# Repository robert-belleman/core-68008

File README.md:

# core-68008
Single-board 68008 system with a Elektor Junior bus interface

The core68008 board is a complete MC68008 computer on one 160 x 100 mm,
4-layer PCB: CPU, 512K RAM, 256K flash, a 68681 DUART for the serial console
and a bridge that runs cards for the Elektor Junior bus at 1 MHz. It boots
into the MON68K monitor, which includes Enhanced BASIC.

Status (2026-11-24): the first PCBs are built and run the monitor from
flash over the FTDI serial link. See [Known issues](#known-issues-and-changes-for-the-next-revision)
for the fixes made on the bench.

## Specifications

| | |
|---|---|
| CPU | MC68008P8 (48-pin DIP, 20 address lines), 8 MHz from oscillator X1 |
| RAM | 512K static RAM, AS6C4008-55 (U4) |
| ROM | 256K flash, SST39SF020A-70 PLCC-32 (U5), programmable in circuit |
| Serial | MC68681 DUART (U6), 3.6864 MHz crystal Y1. Channel A is the console on J2 (FTDI TTL-232R-5V pinout), 38400 8N1, RTS/CTS |
| Expansion | Elektor Junior bus on J1 (DIN 41612, a+c), 64K window at $C0000, 1 MHz PHI2 |
| Glue logic | three ATF22V10C GALs (see below) and a 74LS07 |
| Reset | DS1233-5 power-on reset (U14) and reset button SW1 |
| Interrupts | level 5 = 68681 (vectored), level 2 = Junior IRQ, level 7 = Junior NMI (autovectored) |
| Other | logic analyser header J4, DUART I/O header J3, prototyping area PROTO1 (7 x 20 holes) |

## Memory map

| Range | Device |
|---|---|
| $00000-$7FFFF | SRAM (at reset the boot overlay maps the flash here for reads) |
| $80000-$BFFFF | Flash: MON68K at $80000, EhBASIC at $A0000 |
| $C0000-$CFFFF | Junior bus window (1 MHz bus cycles) |
| $D0000-$EFFFF | unused, bus error |
| $F0000-$FFFFF | 68681 DUART (16 registers, repeated) |

The boot overlay is set by the power-on reset and switched off by the first
access to $80000-$BFFFF, so the CPU fetches its reset vectors from flash.
The monitor's own view of this map, with its workspace and the default
user registers, is in [monitor/MONITOR.md](monitor/MONITOR.md#memory-map-as-the-monitor-sees-it).

## Hardware

The schematic is a hierarchical KiCad 10 project, `core68008.kicad_pro`:

| Sheet | Contents |
|---|---|
| `cpu.kicad_sch` | MC68008 (U1), 74LS07 open-collector drivers (U12), pull-ups, LEDs HALT, RESET and BERR, logic analyser header J4 |
| `memory.kicad_sch` | GAL1 decode (U2), SRAM (U4), flash (U5) |
| `duart.kicad_sch` | 68681 (U6) with crystal Y1, FTDI header J2 (JP3 connects the cable's 5V), I/O header J3, LEDs D5 (OP6) and D6 (OP7) |
| `bridge.kicad_sch` | GAL2 bridge (U3), GAL3 busdbg (U11), 74LS245 buffers (U7-U9), 74HCT573 read latch (U10), Junior bus connector J1 |
| `power.kicad_sch` | 8 MHz oscillator X1, DS1233 reset (U14), reset button, decoupling |

The PCB is `core68008.kicad_pcb`; extra footprints are in `core68008.pretty/`.

### GALs

The GAL sources are in [gal/](gal/) and are built with galasm 2.1
(`make`, `make prog-decode` etc., see the header of [gal/Makefile](gal/Makefile)).
Each `.pld` file explains its equations.

| GAL | Source | Function |
|---|---|---|
| GAL1 (U2) | [decode.pld](gal/decode.pld) | address decoding, boot overlay, DTACK, BERR, RAM/ROM/DUART selects, /RD and /WR |
| GAL2 (U3) | [bridge.pld](gal/bridge.pld) | Junior bus bridge: PHI2 = CLK/8 (1 MHz, locked to the CPU clock), buffer enables, read latch, DTACK after PHI2 falls; interrupt acknowledge (VPA) |
| GAL3 (U11) | [busdbg.pld](gal/busdbg.pld) | bus clocks PHI1/PHI2, bus R/W, RAM.RW, sticky BERR LED, logic analyser trigger and debug outputs DBG0-DBG3 |
| GAL1 (temporary) | [decode_boot.pld](gal/decode_boot.pld) | only for FLASHBOOT, with a 27128 EPROM in the SRAM socket |

### LEDs

| LED | Meaning |
|---|---|
| D2 | power |
| D3, D4 | HALT, RESET |
| D7 | bus error has happened since reset (latched by GAL3) |
| D6 | 68681 OP7: monitor active |
| D5 | 68681 OP6: user LED |

## Software

| Directory | What it is | Documentation |
|---|---|---|
| [monitor/](monitor/) | MON68K, the ROM monitor: memory and register commands, S-record loading (`LO`), disassembler, breakpoints, tracing, a TRAP #15 API for user programs, and `FL` to reprogram the flash from RAM | [MONITOR.md](monitor/MONITOR.md) |
| [monitor/basic/](monitor/basic/) | Lee Davison's Enhanced BASIC 3.54 at $A0000. Start it with `BA` (cold) or `BW` (warm); `BYE` returns to the monitor | [MONITOR.md, EhBASIC](monitor/MONITOR.md#ehbasic-ba-bw) |
| [monitor/flashupd/](monitor/flashupd/) | FLASHUPD: loads a new monitor into the flash from a monitor that doesn't have `FL` yet | [MONITOR.md, FLASHUPD](monitor/MONITOR.md#the-first-time-flashupd) |
| [monitor/examples/](monitor/examples/) | example user programs and the API include file `mon68k.inc` | [MONITOR.md, API](monitor/MONITOR.md#api-for-user-programs-trap-15) |
| [monitor/test/](monitor/test/) | board emulator (Musashi core, with 68681 and SST39SF020A models) and test scripts | [test/README.md](monitor/test/README.md) |
| [flashboot/](flashboot/) | SERTEST and FLASHBOOT: program the flash in circuit from a 27128 EPROM in the SRAM socket, plus `term.py`, a terminal for odd baud rates on macOS | [flashboot/README.md](flashboot/README.md) |
| [Basic/](Basic/) | BASIC programs (a Mandelbrot plot) | |
| [breadboard/](breadboard/) | test programs and logs from the earlier breadboard version | [review.md](breadboard/review.md) |

### Tools

* [vasm](http://sun.hasenbraten.de/vasm/) (`vasmm68k_mot`, Motorola syntax) for all 68000 code. The Makefiles expect `/opt/homebrew/bin/vasmm68k_mot`; override with `make VASM=...`.
* galasm 2.1 for the GALs (`make GALASM=...` to override).
* A T48 programmer with `minipro` for the GALs, the EPROM and the flash (the flash needs a PLCC32 adapter).
* Python 3 for the host scripts (`flashboot.py`, `term.py`, `bin2srec.py`).

### Quick start

```
cd monitor && make          # monitor.bin, the 256K flash image
make flash                  # program it with the T48, or:
make s28                    # monitor.s28, to load with LO and program with FL
```

Connect the FTDI cable to J2 and open a terminal at 38400 8N1 with RTS/CTS.
After reset the monitor shows its banner and the `>` prompt; `HE` lists the
commands. To put a monitor with `FL` on a board whose monitor doesn't have
`FL` yet, use FLASHUPD (`make flashupd`); on a blank board use the T48 or
FLASHBOOT.

## Known issues and changes for the next revision

Found during bring-up of the first PCBs:

* **RxDA pull-up too strong.** The USB-serial module's TX could only pull
  RxDA (via the 10k in RN2) down to about 2.4 V, so the 68681 received
  nothing. Workaround: RN2 removed. Next revision: a separate 100k pull-up on RxDA.
* **~BR floats** now that RN2 is out, because RN2 also pulls up ~BR. Refit RN2
  with its RxDA pin clipped, or fit a 10k pull-up on ~BR.
* **68681 crystal doesn't start reliably** (it runs at about 100 kHz unless the
  board is touched). The 68681 data sheet asks for unequal load capacitors,
  but C2 and C3 are both 22 pF. Change C2 (X1, pin 32) to 12-15 pF and C3
  (X2, pin 33) to 0-5 pF. 12 pF and 4.7 pF are verified to work. An option for a
  3.6864 MHz oscillator can would also help.
* **~VPA and ~IACK5** are driven only by GAL2 and have no pull-ups, so they
  float when GAL2 is not fitted. Add pull-ups.
* **XDTACK** pull-up: use a separate 1k resistor instead of the RN1 element.

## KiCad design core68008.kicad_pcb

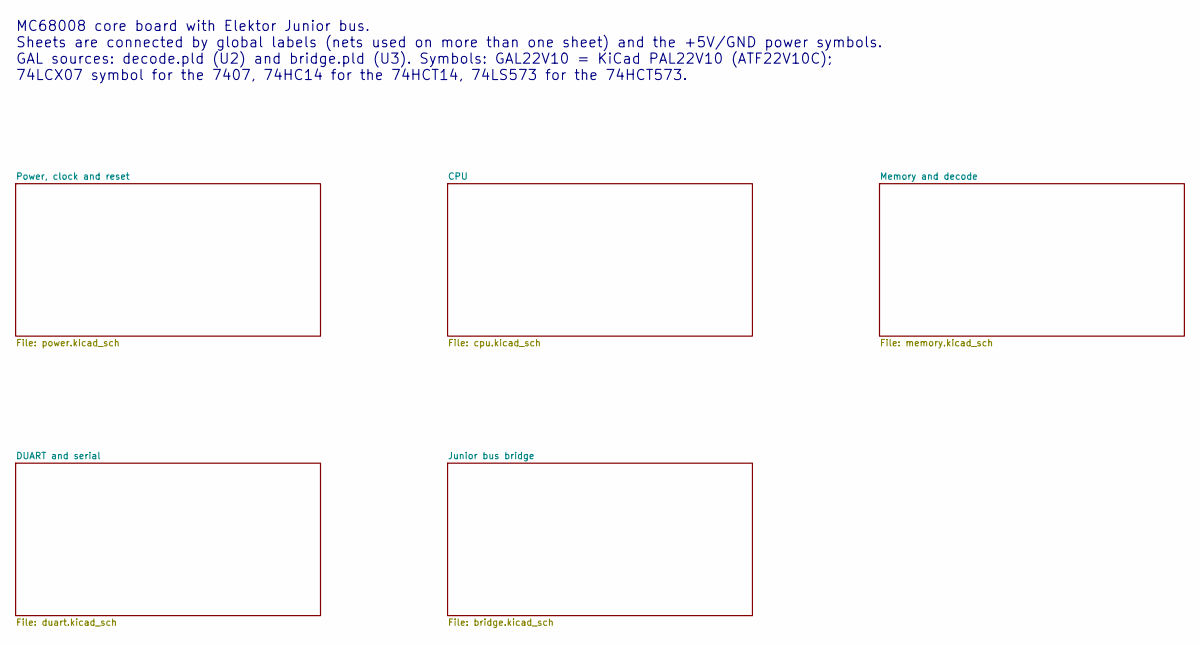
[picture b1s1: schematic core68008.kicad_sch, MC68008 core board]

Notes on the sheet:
MC68008 core board with Elektor Junior bus. Sheets are connected by global labels (nets used on more than one sheet) and the +5V/GND power symbols. GAL sources: decode.pld (U2) and bridge.pld (U3). Symbols: GAL22V10 = KiCad PAL22V10 (ATF22V10C); 74LCX07 symbol for the 7407, 74HC14 for the 74HCT14, 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

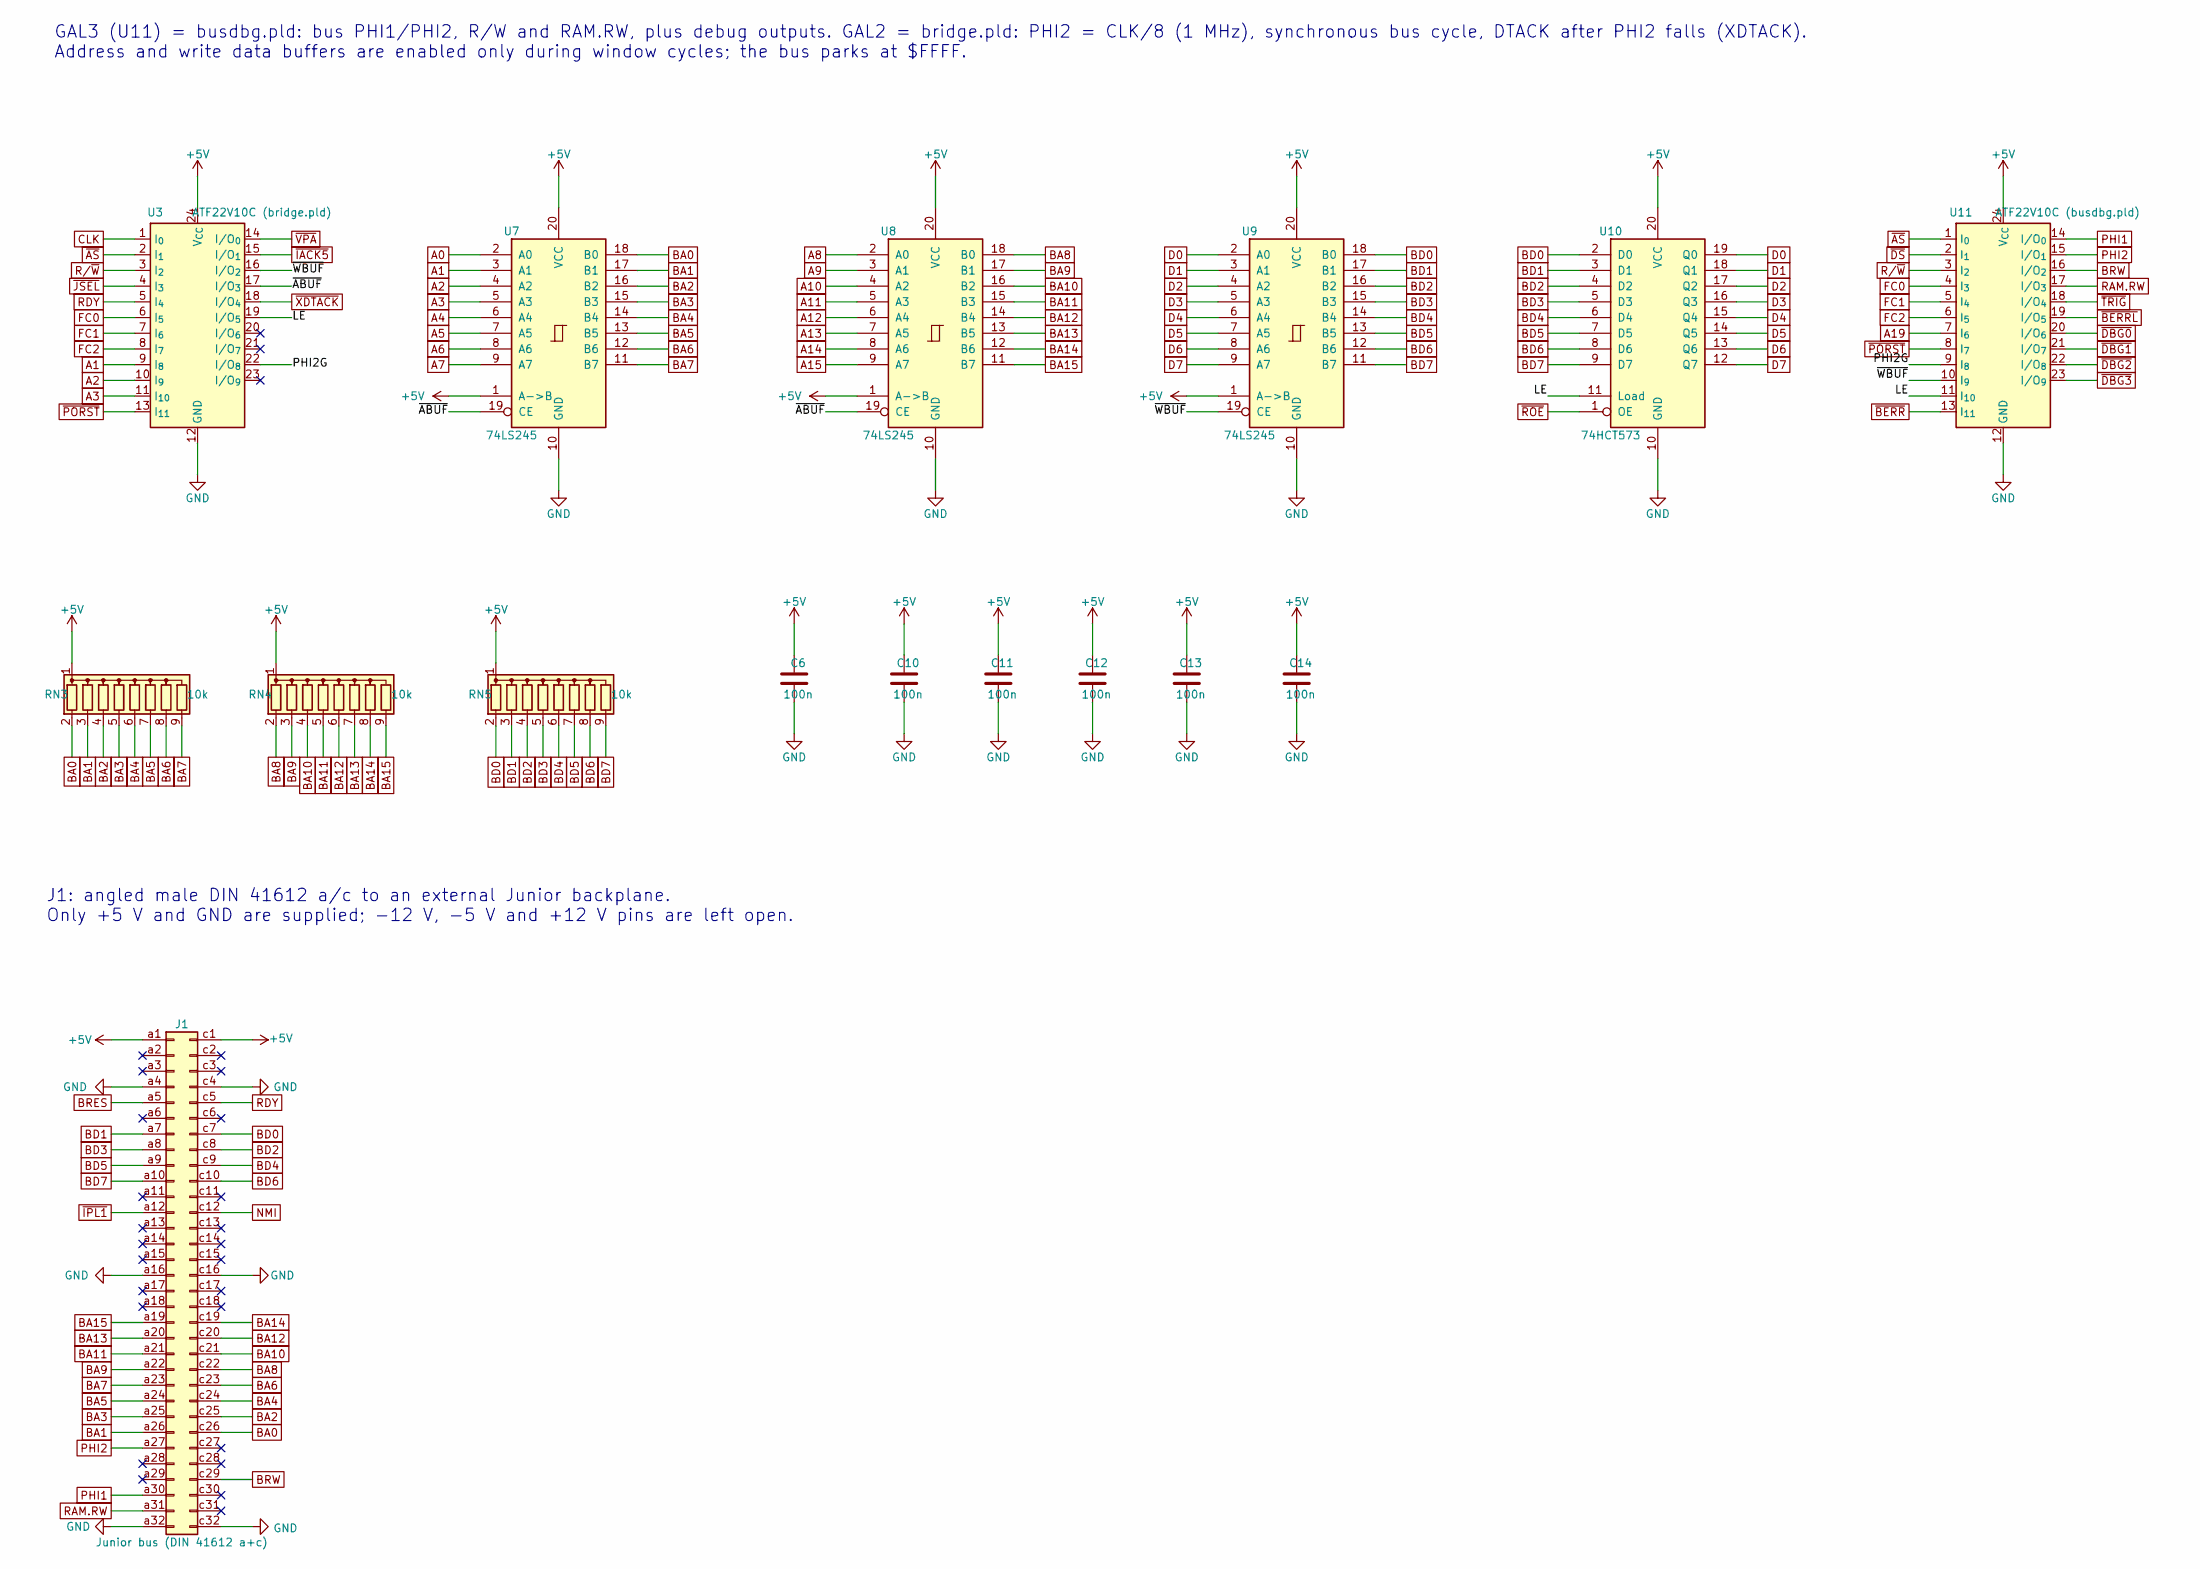
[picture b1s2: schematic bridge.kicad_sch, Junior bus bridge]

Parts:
C6, C10, C11, C12, C13, C14: 100n; C_Disc_D5.0mm_W2.5mm_P5.00mm
J1: Junior bus (DIN 41612 a+c); DIN41612_C_2x32_Male_Horizontal_THT_LongPads
RN3, RN4, RN5: 10k; R_Array_SIP9
U3: ATF22V10C (bridge.pld); DIP-24_W7.62mm_Socket_LongPads
U7, U8, U9: 74LS245; DIP-20_W7.62mm_Socket_LongPads
U10: 74HCT573; DIP-20_W7.62mm_Socket_LongPads
U11: ATF22V10C (busdbg.pld); DIP-24_W7.62mm_Socket_LongPads

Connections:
+5V: C6.1, C10.1, C11.1, C12.1, C13.1, C14.1, J1.a1, J1.c1, RN3.1 (common), RN4.1 (common), RN5.1 (common), U3.24 (V_{CC}), U7.1 (A->B), U7.20 (VCC), U8.1 (A->B), U8.20 (VCC), U9.1 (A->B), U9.20 (VCC), U10.20 (VCC), U11.24 (V_{CC}); also elsewhere on the board
/Junior bus bridge/LE: U3.19 (I/O_{5}), U10.11 (Load), U11.11 (I_{10})
/Junior bus bridge/PHI2G: U3.22 (I/O_{8}), U11.9 (I_{8})
/Junior bus bridge/~ABUF: U3.17 (I/O_{3}), U7.19 (CE), U8.19 (CE)
/Junior bus bridge/~WBUF: U3.16 (I/O_{2}), U9.19 (CE), U11.10 (I_{9})
A0: U7.2 (A0); also elsewhere on the board
A1: U3.9 (I_{8}), U7.3 (A1); also elsewhere on the board
A2: U3.10 (I_{9}), U7.4 (A2); also elsewhere on the board
A3: U3.11 (I_{10}), U7.5 (A3); also elsewhere on the board
A4: U7.6 (A4); also elsewhere on the board
A5: U7.7 (A5); also elsewhere on the board
A6: U7.8 (A6); also elsewhere on the board
A7: U7.9 (A7); also elsewhere on the board
A8: U8.2 (A0); also elsewhere on the board
A9: U8.3 (A1); also elsewhere on the board
A10: U8.4 (A2); also elsewhere on the board
A11: U8.5 (A3); also elsewhere on the board
A12: U8.6 (A4); also elsewhere on the board
A13: U8.7 (A5); also elsewhere on the board
A14: U8.8 (A6); also elsewhere on the board
A15: U8.9 (A7); also elsewhere on the board
A19: U11.7 (I_{6}); also elsewhere on the board
BA0: J1.c26, RN3.2 (R1), U7.18 (B0)
BA1: J1.a26, RN3.3 (R2), U7.17 (B1)
BA2: J1.c25, RN3.4 (R3), U7.16 (B2)
BA3: J1.a25, RN3.5 (R4), U7.15 (B3)
BA4: J1.c24, RN3.6 (R5), U7.14 (B4)
BA5: J1.a24, RN3.7 (R6), U7.13 (B5)
BA6: J1.c23, RN3.8 (R7), U7.12 (B6)
BA7: J1.a23, RN3.9 (R8), U7.11 (B7)
BA8: J1.c22, RN4.2 (R1), U8.18 (B0)
BA9: J1.a22, RN4.3 (R2), U8.17 (B1)
BA10: J1.c21, RN4.4 (R3), U8.16 (B2)
BA11: J1.a21, RN4.5 (R4), U8.15 (B3)
BA12: J1.c20, RN4.6 (R5), U8.14 (B4)
BA13: J1.a20, RN4.7 (R6), U8.13 (B5)
BA14: J1.c19, RN4.8 (R7), U8.12 (B6)
BA15: J1.a19, RN4.9 (R8), U8.11 (B7)
BD0: J1.c7, RN5.2 (R1), U9.18 (B0), U10.2 (D0)
BD1: J1.a7, RN5.3 (R2), U9.17 (B1), U10.3 (D1)
BD2: J1.c8, RN5.4 (R3), U9.16 (B2), U10.4 (D2)
BD3: J1.a8, RN5.5 (R4), U9.15 (B3), U10.5 (D3)
BD4: J1.c9, RN5.6 (R5), U9.14 (B4), U10.6 (D4)
BD5: J1.a9, RN5.7 (R6), U9.13 (B5), U10.7 (D5)
BD6: J1.c10, RN5.8 (R7), U9.12 (B6), U10.8 (D6)
BD7: J1.a10, RN5.9 (R8), U9.11 (B7), U10.9 (D7)
BRES: J1.a5; also elsewhere on the board
BRW: J1.c29, U11.16 (I/O_{2})
CLK: U3.1 (I_{0}); also elsewhere on the board
D0: U9.2 (A0), U10.19 (Q0); also elsewhere on the board
D1: U9.3 (A1), U10.18 (Q1); also elsewhere on the board
D2: U9.4 (A2), U10.17 (Q2); also elsewhere on the board
D3: U9.5 (A3), U10.16 (Q3); also elsewhere on the board
D4: U9.6 (A4), U10.15 (Q4); also elsewhere on the board
D5: U9.7 (A5), U10.14 (Q5); also elsewhere on the board
D6: U9.8 (A6), U10.13 (Q6); also elsewhere on the board
D7: U9.9 (A7), U10.12 (Q7); also elsewhere on the board
FC0: U3.6 (I_{5}), U11.4 (I_{3}); also elsewhere on the board
FC1: U3.7 (I_{6}), U11.5 (I_{4}); also elsewhere on the board
FC2: U3.8 (I_{7}), U11.6 (I_{5}); also elsewhere on the board
GND: C6.2, C10.2, C11.2, C12.2, C13.2, C14.2, J1.a4, J1.a16, J1.a32, J1.c4, J1.c16, J1.c32, U3.12 (GND), U7.10 (GND), U8.10 (GND), U9.10 (GND), U10.10 (GND), U11.12 (GND); also elsewhere on the board
NMI: J1.c12; also elsewhere on the board
PHI1: J1.a30, U11.14 (I/O_{0})
PHI2: J1.a27, U11.15 (I/O_{1}); also elsewhere on the board
RAM.RW: J1.a31, U11.17 (I/O_{3})
RDY: J1.c5, U3.5 (I_{4}); also elsewhere on the board
R/~W: U3.3 (I_{2}), U11.3 (I_{2}); also elsewhere on the board
~AS: U3.2 (I_{1}), U11.1 (I_{0}); also elsewhere on the board
~BERRL: U11.19 (I/O_{5}); also elsewhere on the board
~BERR: U11.13 (I_{11}); also elsewhere on the board
~DBG0: U11.20 (I/O_{6}); also elsewhere on the board
~DBG1: U11.21 (I/O_{7}); also elsewhere on the board
~DBG2: U11.22 (I/O_{8}); also elsewhere on the board
~DBG3: U11.23 (I/O_{9}); also elsewhere on the board
~DS: U11.2 (I_{1}); also elsewhere on the board
~IACK5: U3.15 (I/O_{1}); also elsewhere on the board
~IPL1: J1.a12; also elsewhere on the board
~JSEL: U3.4 (I_{3}); also elsewhere on the board
~PORST: U3.13 (I_{11}), U11.8 (I_{7}); also elsewhere on the board
~ROE: U10.1 (OE); also elsewhere on the board
~TRIG: U11.18 (I/O_{4}); also elsewhere on the board
~VPA: U3.14 (I/O_{0}); also elsewhere on the board
~XDTACK: U3.18 (I/O_{4}); also elsewhere on the board

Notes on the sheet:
J1: angled male DIN 41612 a/c to an external Junior backplane. Only +5 V and GND are supplied; -12 V, -5 V and +12 V pins are left open.
GAL3 (U11) = busdbg.pld: bus PHI1/PHI2, R/W and RAM.RW, plus debug outputs. GAL2 = bridge.pld: PHI2 = CLK/8 (1 MHz), synchronous bus cycle, DTACK after PHI2 falls (XDTACK). Address and write data buffers are enabled only during window cycles; the bus parks at $FFFF.

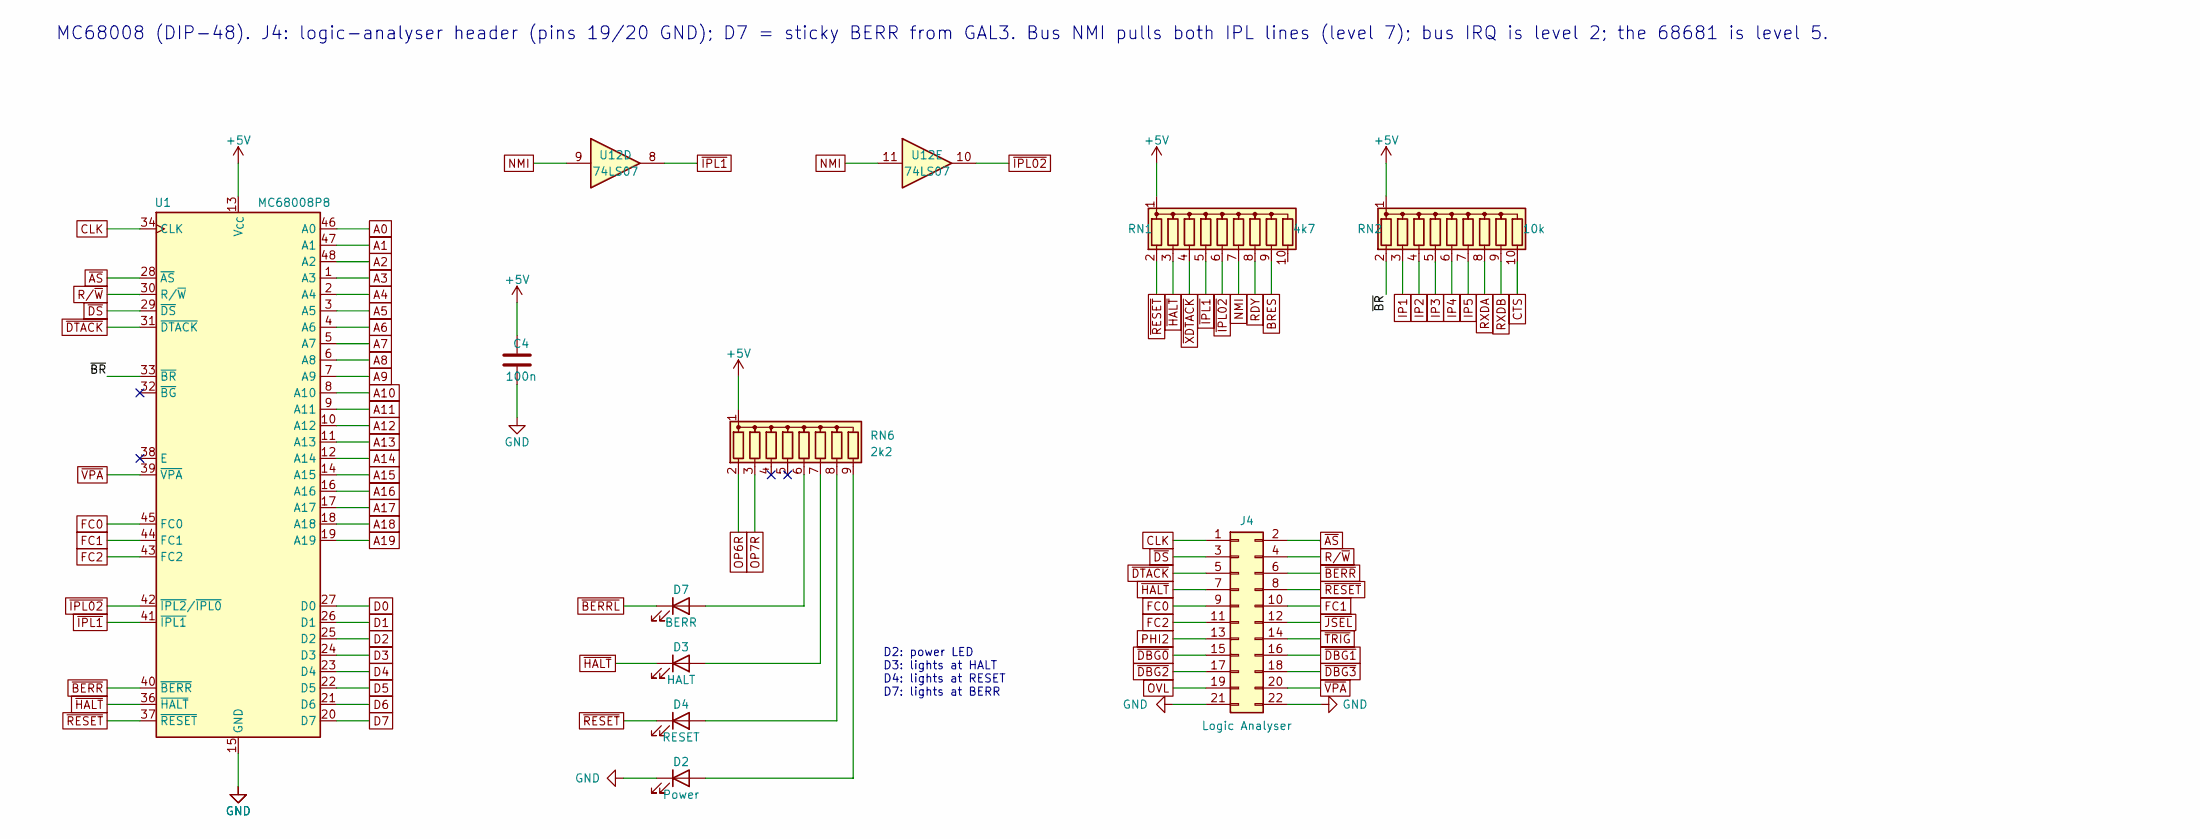
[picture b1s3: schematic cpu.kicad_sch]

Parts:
C4: 100n; C_Disc_D5.0mm_W2.5mm_P5.00mm
D2: Power; LED_D3.0mm
D3: HALT; LED_D3.0mm
D4: RESET; LED_D3.0mm
D7: BERR; LED_D3.0mm
J4: Logic Analyser; PinHeader_2x11_P2.54mm_Vertical
RN1: 4k7; R_Array_SIP10
RN2: 10k; R_Array_SIP10
RN6: 2k2; R_Array_SIP9
U1: MC68008P8; DIP-48_W15.24mm_Socket_LongPads
U12: 74LS07; DIP-14_W7.62mm_Socket_LongPads

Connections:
+5V: C4.1, RN1.1 (common), RN2.1 (common), RN6.1 (common), U1.13 (V_{CC}); also elsewhere on the board
/CPU/~BR: RN2.2 (R1), U1.33 (~BR)
A0: U1.46 (A0); also elsewhere on the board
A1: U1.47 (A1); also elsewhere on the board
A2: U1.48 (A2); also elsewhere on the board
A3: U1.1 (A3); also elsewhere on the board
A4: U1.2 (A4); also elsewhere on the board
A5: U1.3 (A5); also elsewhere on the board
A6: U1.4 (A6); also elsewhere on the board
A7: U1.5 (A7); also elsewhere on the board
A8: U1.6 (A8); also elsewhere on the board
A9: U1.7 (A9); also elsewhere on the board
A10: U1.8 (A10); also elsewhere on the board
A11: U1.9 (A11); also elsewhere on the board
A12: U1.10 (A12); also elsewhere on the board
A13: U1.11 (A13); also elsewhere on the board
A14: U1.12 (A14); also elsewhere on the board
A15: U1.14 (A15); also elsewhere on the board
A16: U1.16 (A16); also elsewhere on the board
A17: U1.17 (A17); also elsewhere on the board
A18: U1.18 (A18); also elsewhere on the board
A19: U1.19 (A19); also elsewhere on the board
BRES: RN1.9 (R8); also elsewhere on the board
CLK: J4.1, U1.34 (CLK); also elsewhere on the board
CTS: RN2.10 (R9); also elsewhere on the board
D0: U1.27 (D0); also elsewhere on the board
D1: U1.26 (D1); also elsewhere on the board
D2: U1.25 (D2); also elsewhere on the board
D3: U1.24 (D3); also elsewhere on the board
D4: U1.23 (D4); also elsewhere on the board
D5: U1.22 (D5); also elsewhere on the board
D6: U1.21 (D6); also elsewhere on the board
D7: U1.20 (D7); also elsewhere on the board
FC0: J4.9, U1.45 (FC0); also elsewhere on the board
FC1: J4.10, U1.44 (FC1); also elsewhere on the board
FC2: J4.11, U1.43 (FC2); also elsewhere on the board
GND: C4.2, D2.1 (K), J4.21, J4.22, U1.15 (GND), U1.35 (GND); also elsewhere on the board
IP1: RN2.3 (R2); also elsewhere on the board
IP2: RN2.4 (R3); also elsewhere on the board
IP3: RN2.5 (R4); also elsewhere on the board
IP4: RN2.6 (R5); also elsewhere on the board
IP5: RN2.7 (R6); also elsewhere on the board
NMI: RN1.7 (R6), U12.9, U12.11; also elsewhere on the board
unnamed: D2.2 (A), RN6.9 (R8)
unnamed: D3.2 (A), RN6.7 (R6)
unnamed: D4.2 (A), RN6.8 (R7)
unnamed: D7.2 (A), RN6.6 (R5)
OP6R: RN6.2 (R1); also elsewhere on the board
OP7R: RN6.3 (R2); also elsewhere on the board
OVL: J4.19; also elsewhere on the board
PHI2: J4.13; also elsewhere on the board
RDY: RN1.8 (R7); also elsewhere on the board
RXDA: RN2.8 (R7); also elsewhere on the board
RXDB: RN2.9 (R8); also elsewhere on the board
R/~W: J4.4, U1.30 (R/~W); also elsewhere on the board
~AS: J4.2, U1.28 (~AS); also elsewhere on the board
~BERRL: D7.1 (K); also elsewhere on the board
~BERR: J4.6, U1.40 (~BERR); also elsewhere on the board
~DBG0: J4.15; also elsewhere on the board
~DBG1: J4.16; also elsewhere on the board
~DBG2: J4.17; also elsewhere on the board
~DBG3: J4.18; also elsewhere on the board
~DS: J4.3, U1.29 (~DS); also elsewhere on the board
~DTACK: J4.5, U1.31 (~DTACK); also elsewhere on the board
~HALT: D3.1 (K), J4.7, RN1.3 (R2), U1.36 (~HALT); also elsewhere on the board
~IPL1: RN1.5 (R4), U1.41 (~IPL1), U12.8; also elsewhere on the board
~IPL02: RN1.6 (R5), U1.42 (~IPL2/~IPL0), U12.10; also elsewhere on the board
~JSEL: J4.12; also elsewhere on the board
~RESET: D4.1 (K), J4.8, RN1.2 (R1), U1.37 (~RESET); also elsewhere on the board
~TRIG: J4.14; also elsewhere on the board
~VPA: J4.20, U1.39 (~VPA); also elsewhere on the board
~XDTACK: RN1.4 (R3); also elsewhere on the board

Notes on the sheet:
MC68008 (DIP-48). J4: logic-analyser header (pins 19/20 GND); D7 = sticky BERR from GAL3. Bus NMI pulls both IPL lines (level 7); bus IRQ is level 2; the 68681 is level 5.
D2: power LED D3: lights at HALT D4: lights at RESET D7: lights at BERR

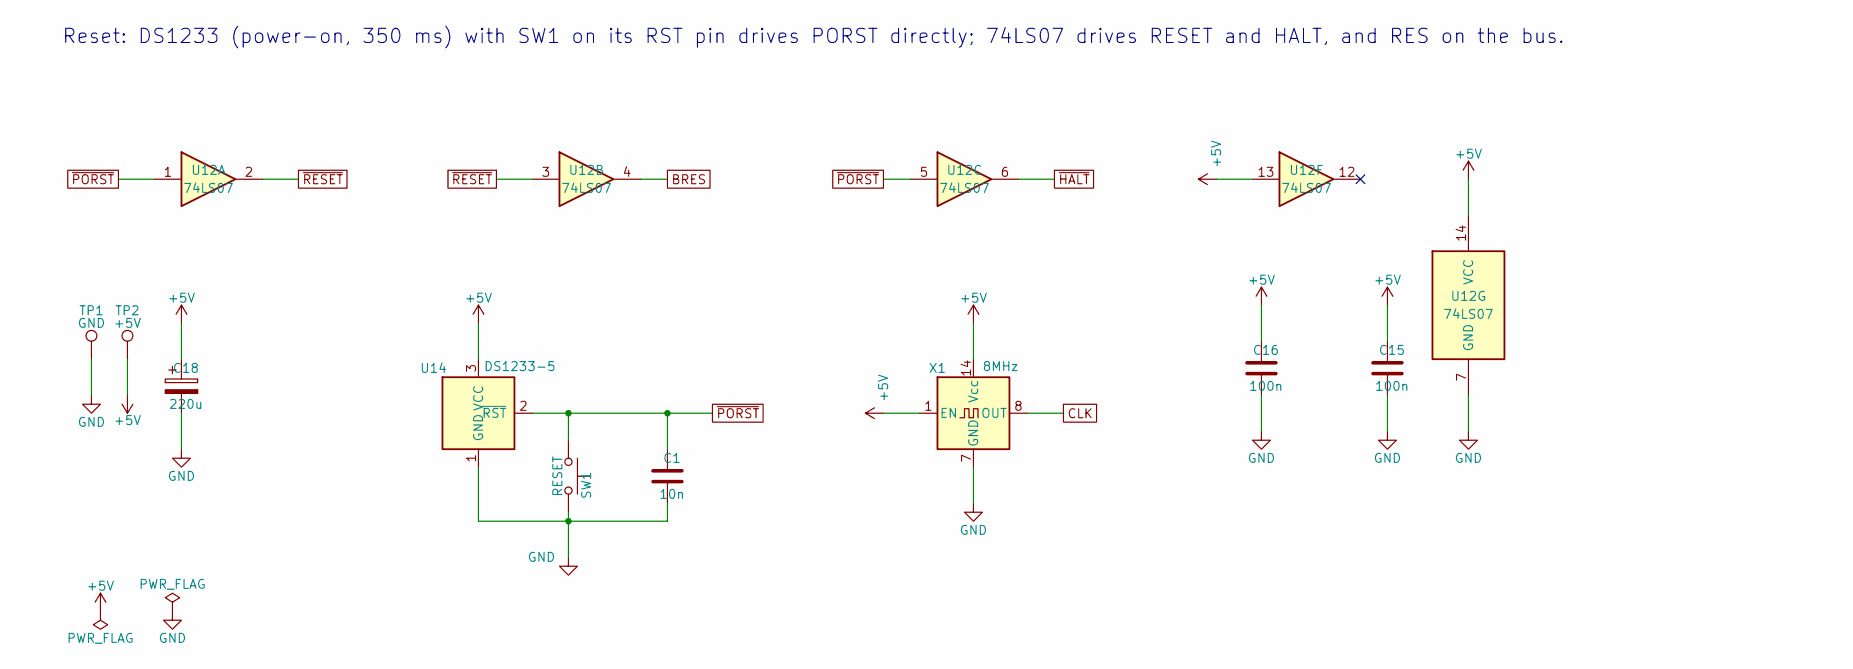
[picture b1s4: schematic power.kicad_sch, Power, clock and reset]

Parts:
C1: 10n; C_Disc_D5.0mm_W2.5mm_P5.00mm
C15, C16: 100n; C_Disc_D5.0mm_W2.5mm_P5.00mm
C18: 220u; CP_Radial_D8.0mm_P3.50mm
SW1: RESET; SW_PUSH_6mm
TP1: GND; TestPoint_Loop_D2.50mm_Drill1.0mm
TP2: +5V; TestPoint_Loop_D2.50mm_Drill1.0mm
U12: 74LS07; DIP-14_W7.62mm_Socket_LongPads
U14: DS1233-5; TO-92_Inline
X1: 8MHz; Oscillator_DIP-14_LargePads

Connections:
+5V: C15.1, C16.1, C18.1, TP2.1 (1_1), U12.13, U12.14 (VCC), U14.3 (VCC), X1.1 (EN), X1.14 (Vcc); also elsewhere on the board
BRES: U12.4; also elsewhere on the board
CLK: X1.8 (OUT); also elsewhere on the board
GND: C1.2, C15.2, C16.2, C18.2, SW1.2, TP1.1 (1_1), U12.7 (GND), U14.1 (GND), X1.7 (GND); also elsewhere on the board
~HALT: U12.6; also elsewhere on the board
~PORST: C1.1, SW1.1, U12.1, U12.5, U14.2 (~RST); also elsewhere on the board
~RESET: U12.2, U12.3; also elsewhere on the board

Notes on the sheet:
Reset: DS1233 (power-on, 350 ms) with SW1 on its RST pin drives PORST directly; 74LS07 drives RESET and HALT, and RES on the bus.

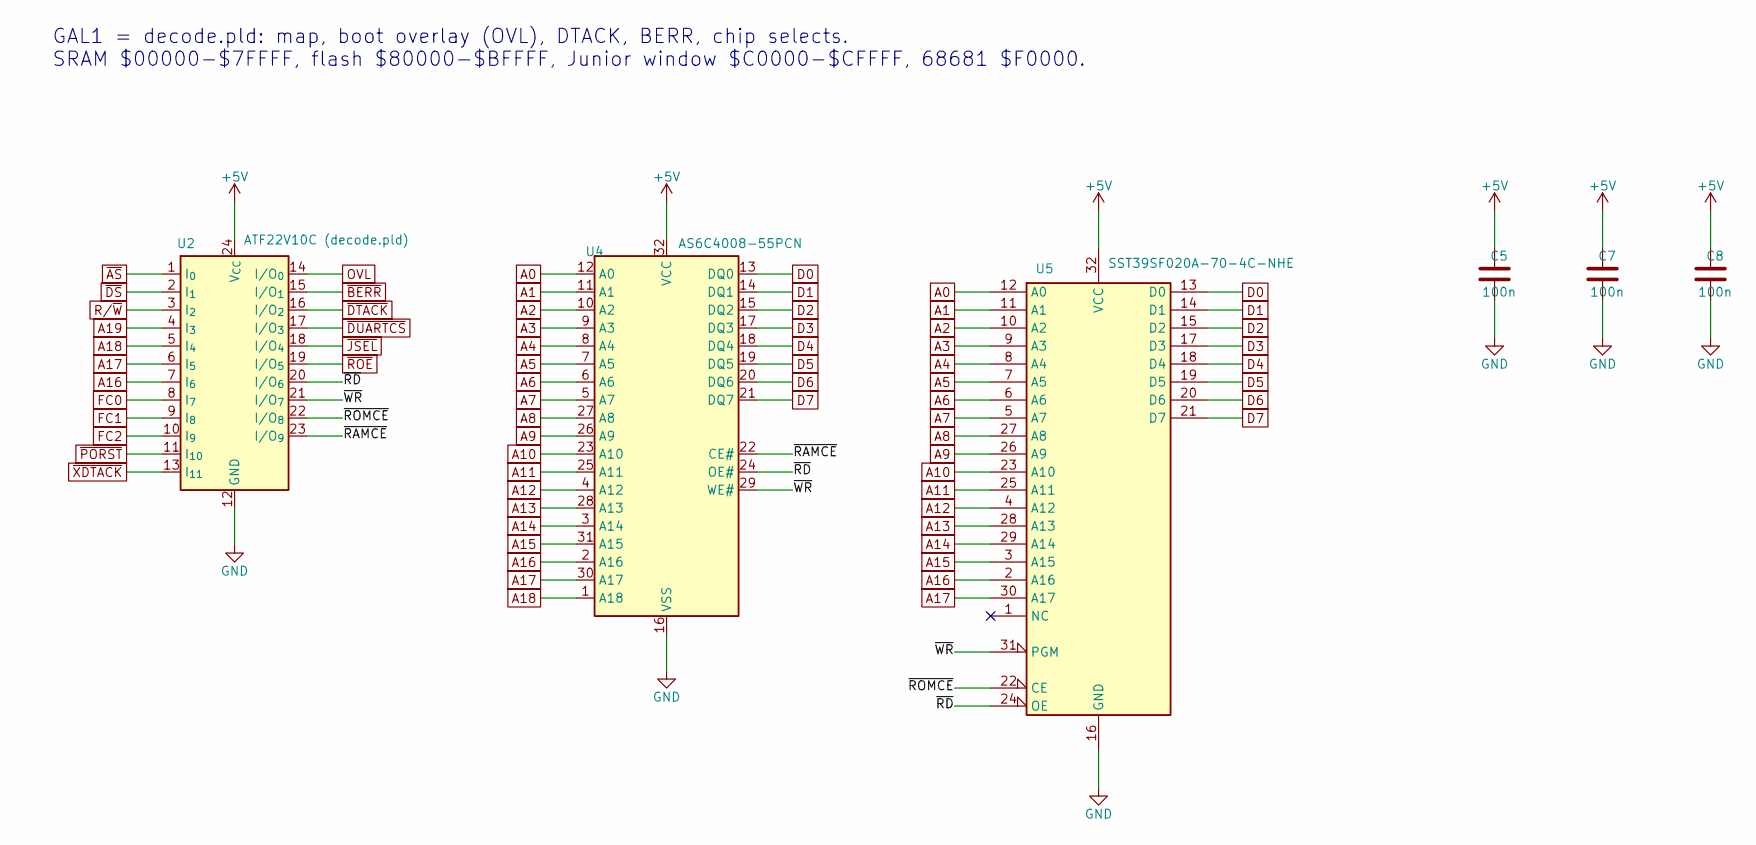
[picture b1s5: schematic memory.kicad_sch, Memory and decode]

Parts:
C5, C7, C8: 100n; C_Disc_D5.0mm_W2.5mm_P5.00mm
U2: ATF22V10C (decode.pld); DIP-24_W7.62mm_Socket_LongPads
U4: AS6C4008-55PCN; DIP-32_W15.24mm_Socket_LongPads
U5: SST39SF020A-70-4C-NHE; PLCC-32_THT-Socket

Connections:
+5V: C5.1, C7.1, C8.1, U2.24 (V_{CC}), U4.32 (VCC), U5.32 (VCC); also elsewhere on the board
/Memory and decode/~RAMCE: U2.23 (I/O_{9}), U4.22 (CE#)
/Memory and decode/~RD: U2.20 (I/O_{6}), U4.24 (OE#), U5.24 (OE)
/Memory and decode/~ROMCE: U2.22 (I/O_{8}), U5.22 (CE)
/Memory and decode/~WR: U2.21 (I/O_{7}), U4.29 (WE#), U5.31 (PGM)
A0: U4.12 (A0), U5.12 (A0); also elsewhere on the board
A1: U4.11 (A1), U5.11 (A1); also elsewhere on the board
A2: U4.10 (A2), U5.10 (A2); also elsewhere on the board
A3: U4.9 (A3), U5.9 (A3); also elsewhere on the board
A4: U4.8 (A4), U5.8 (A4); also elsewhere on the board
A5: U4.7 (A5), U5.7 (A5); also elsewhere on the board
A6: U4.6 (A6), U5.6 (A6); also elsewhere on the board
A7: U4.5 (A7), U5.5 (A7); also elsewhere on the board
A8: U4.27 (A8), U5.27 (A8); also elsewhere on the board
A9: U4.26 (A9), U5.26 (A9); also elsewhere on the board
A10: U4.23 (A10), U5.23 (A10); also elsewhere on the board
A11: U4.25 (A11), U5.25 (A11); also elsewhere on the board
A12: U4.4 (A12), U5.4 (A12); also elsewhere on the board
A13: U4.28 (A13), U5.28 (A13); also elsewhere on the board
A14: U4.3 (A14), U5.29 (A14); also elsewhere on the board
A15: U4.31 (A15), U5.3 (A15); also elsewhere on the board
A16: U2.7 (I_{6}), U4.2 (A16), U5.2 (A16); also elsewhere on the board
A17: U2.6 (I_{5}), U4.30 (A17), U5.30 (A17); also elsewhere on the board
A18: U2.5 (I_{4}), U4.1 (A18); also elsewhere on the board
A19: U2.4 (I_{3}); also elsewhere on the board
D0: U4.13 (DQ0), U5.13 (D0); also elsewhere on the board
D1: U4.14 (DQ1), U5.14 (D1); also elsewhere on the board
D2: U4.15 (DQ2), U5.15 (D2); also elsewhere on the board
D3: U4.17 (DQ3), U5.17 (D3); also elsewhere on the board
D4: U4.18 (DQ4), U5.18 (D4); also elsewhere on the board
D5: U4.19 (DQ5), U5.19 (D5); also elsewhere on the board
D6: U4.20 (DQ6), U5.20 (D6); also elsewhere on the board
D7: U4.21 (DQ7), U5.21 (D7); also elsewhere on the board
FC0: U2.8 (I_{7}); also elsewhere on the board
FC1: U2.9 (I_{8}); also elsewhere on the board
FC2: U2.10 (I_{9}); also elsewhere on the board
GND: C5.2, C7.2, C8.2, U2.12 (GND), U4.16 (VSS), U5.16 (GND); also elsewhere on the board
OVL: U2.14 (I/O_{0}); also elsewhere on the board
R/~W: U2.3 (I_{2}); also elsewhere on the board
~AS: U2.1 (I_{0}); also elsewhere on the board
~BERR: U2.15 (I/O_{1}); also elsewhere on the board
~DS: U2.2 (I_{1}); also elsewhere on the board
~DTACK: U2.16 (I/O_{2}); also elsewhere on the board
~DUARTCS: U2.17 (I/O_{3}); also elsewhere on the board
~JSEL: U2.18 (I/O_{4}); also elsewhere on the board
~PORST: U2.11 (I_{10}); also elsewhere on the board
~ROE: U2.19 (I/O_{5}); also elsewhere on the board
~XDTACK: U2.13 (I_{11}); also elsewhere on the board

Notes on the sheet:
GAL1 = decode.pld: map, boot overlay (OVL), DTACK, BERR, chip selects. SRAM $00000-$7FFFF, flash $80000-$BFFFF, Junior window $C0000-$CFFFF, 68681 $F0000.

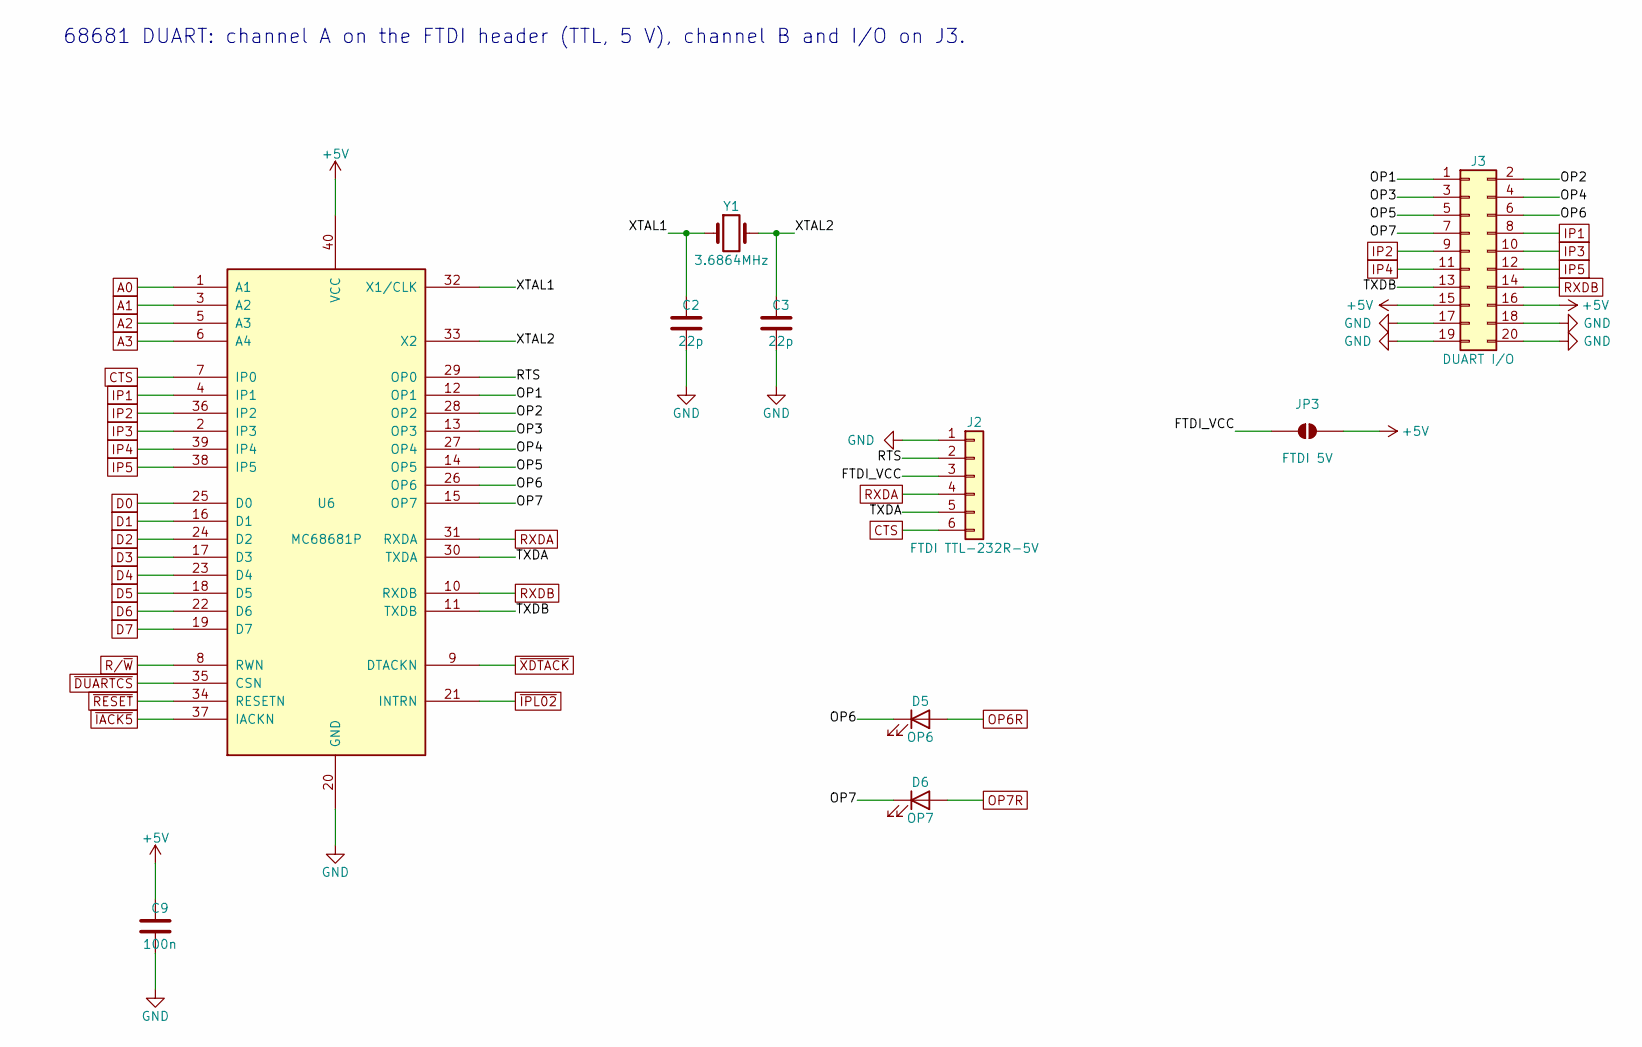
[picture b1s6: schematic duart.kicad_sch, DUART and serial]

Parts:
C2, C3: 22p; C_Disc_D3.0mm_W1.6mm_P2.50mm
C9: 100n; C_Disc_D5.0mm_W2.5mm_P5.00mm
D5: OP6; LED_D3.0mm
D6: OP7; LED_D3.0mm
J2: FTDI TTL-232R-5V; PinHeader_1x06_P2.54mm_Vertical
J3: DUART I/O; PinHeader_2x10_P2.54mm_Vertical
JP3: FTDI 5V; PinHeader_1x02_P2.54mm_Vertical
U6: MC68681P; DIP-40_W15.24mm_Socket_LongPads
Y1: 3.6864MHz; Crystal_HC49-4H_Vertical

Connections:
+5V: C9.1, J3.15, J3.16, JP3.2 (B), U6.40 (VCC); also elsewhere on the board
/DUART and serial/FTDI_VCC: J2.3, JP3.1 (A)
/DUART and serial/OP1: J3.1, U6.12 (OP1)
/DUART and serial/OP2: J3.2, U6.28 (OP2)
/DUART and serial/OP3: J3.3, U6.13 (OP3)
/DUART and serial/OP4: J3.4, U6.27 (OP4)
/DUART and serial/OP5: J3.5, U6.14 (OP5)
/DUART and serial/OP6: D5.1 (K), J3.6, U6.26 (OP6)
/DUART and serial/OP7: D6.1 (K), J3.7, U6.15 (OP7)
/DUART and serial/RTS: J2.2, U6.29 (OP0)
/DUART and serial/TXDA: J2.5, U6.30 (TXDA)
/DUART and serial/TXDB: J3.13, U6.11 (TXDB)
/DUART and serial/XTAL1: C2.1, U6.32 (X1/CLK), Y1.1
/DUART and serial/XTAL2: C3.1, U6.33 (X2), Y1.2
A0: U6.1 (A1); also elsewhere on the board
A1: U6.3 (A2); also elsewhere on the board
A2: U6.5 (A3); also elsewhere on the board
A3: U6.6 (A4); also elsewhere on the board
CTS: J2.6, U6.7 (IP0); also elsewhere on the board
D0: U6.25 (D0); also elsewhere on the board
D1: U6.16 (D1); also elsewhere on the board
D2: U6.24 (D2); also elsewhere on the board
D3: U6.17 (D3); also elsewhere on the board
D4: U6.23 (D4); also elsewhere on the board
D5: U6.18 (D5); also elsewhere on the board
D6: U6.22 (D6); also elsewhere on the board
D7: U6.19 (D7); also elsewhere on the board
GND: C2.2, C3.2, C9.2, J2.1, J3.17, J3.18, J3.19, J3.20, U6.20 (GND); also elsewhere on the board
IP1: J3.8, U6.4 (IP1); also elsewhere on the board
IP2: J3.9, U6.36 (IP2); also elsewhere on the board
IP3: J3.10, U6.2 (IP3); also elsewhere on the board
IP4: J3.11, U6.39 (IP4); also elsewhere on the board
IP5: J3.12, U6.38 (IP5); also elsewhere on the board
OP6R: D5.2 (A); also elsewhere on the board
OP7R: D6.2 (A); also elsewhere on the board
RXDA: J2.4, U6.31 (RXDA); also elsewhere on the board
RXDB: J3.14, U6.10 (RXDB); also elsewhere on the board
R/~W: U6.8 (RWN); also elsewhere on the board
~DUARTCS: U6.35 (CSN); also elsewhere on the board
~IACK5: U6.37 (IACKN); also elsewhere on the board
~IPL02: U6.21 (INTRN); also elsewhere on the board
~RESET: U6.34 (RESETN); also elsewhere on the board
~XDTACK: U6.9 (DTACKN); also elsewhere on the board

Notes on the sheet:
68681 DUART: channel A on the FTDI header (TTL, 5 V), channel B and I/O on J3.

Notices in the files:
core68008.kicad_pcb:
(C) Copyright 2026 by Robert Belleman
